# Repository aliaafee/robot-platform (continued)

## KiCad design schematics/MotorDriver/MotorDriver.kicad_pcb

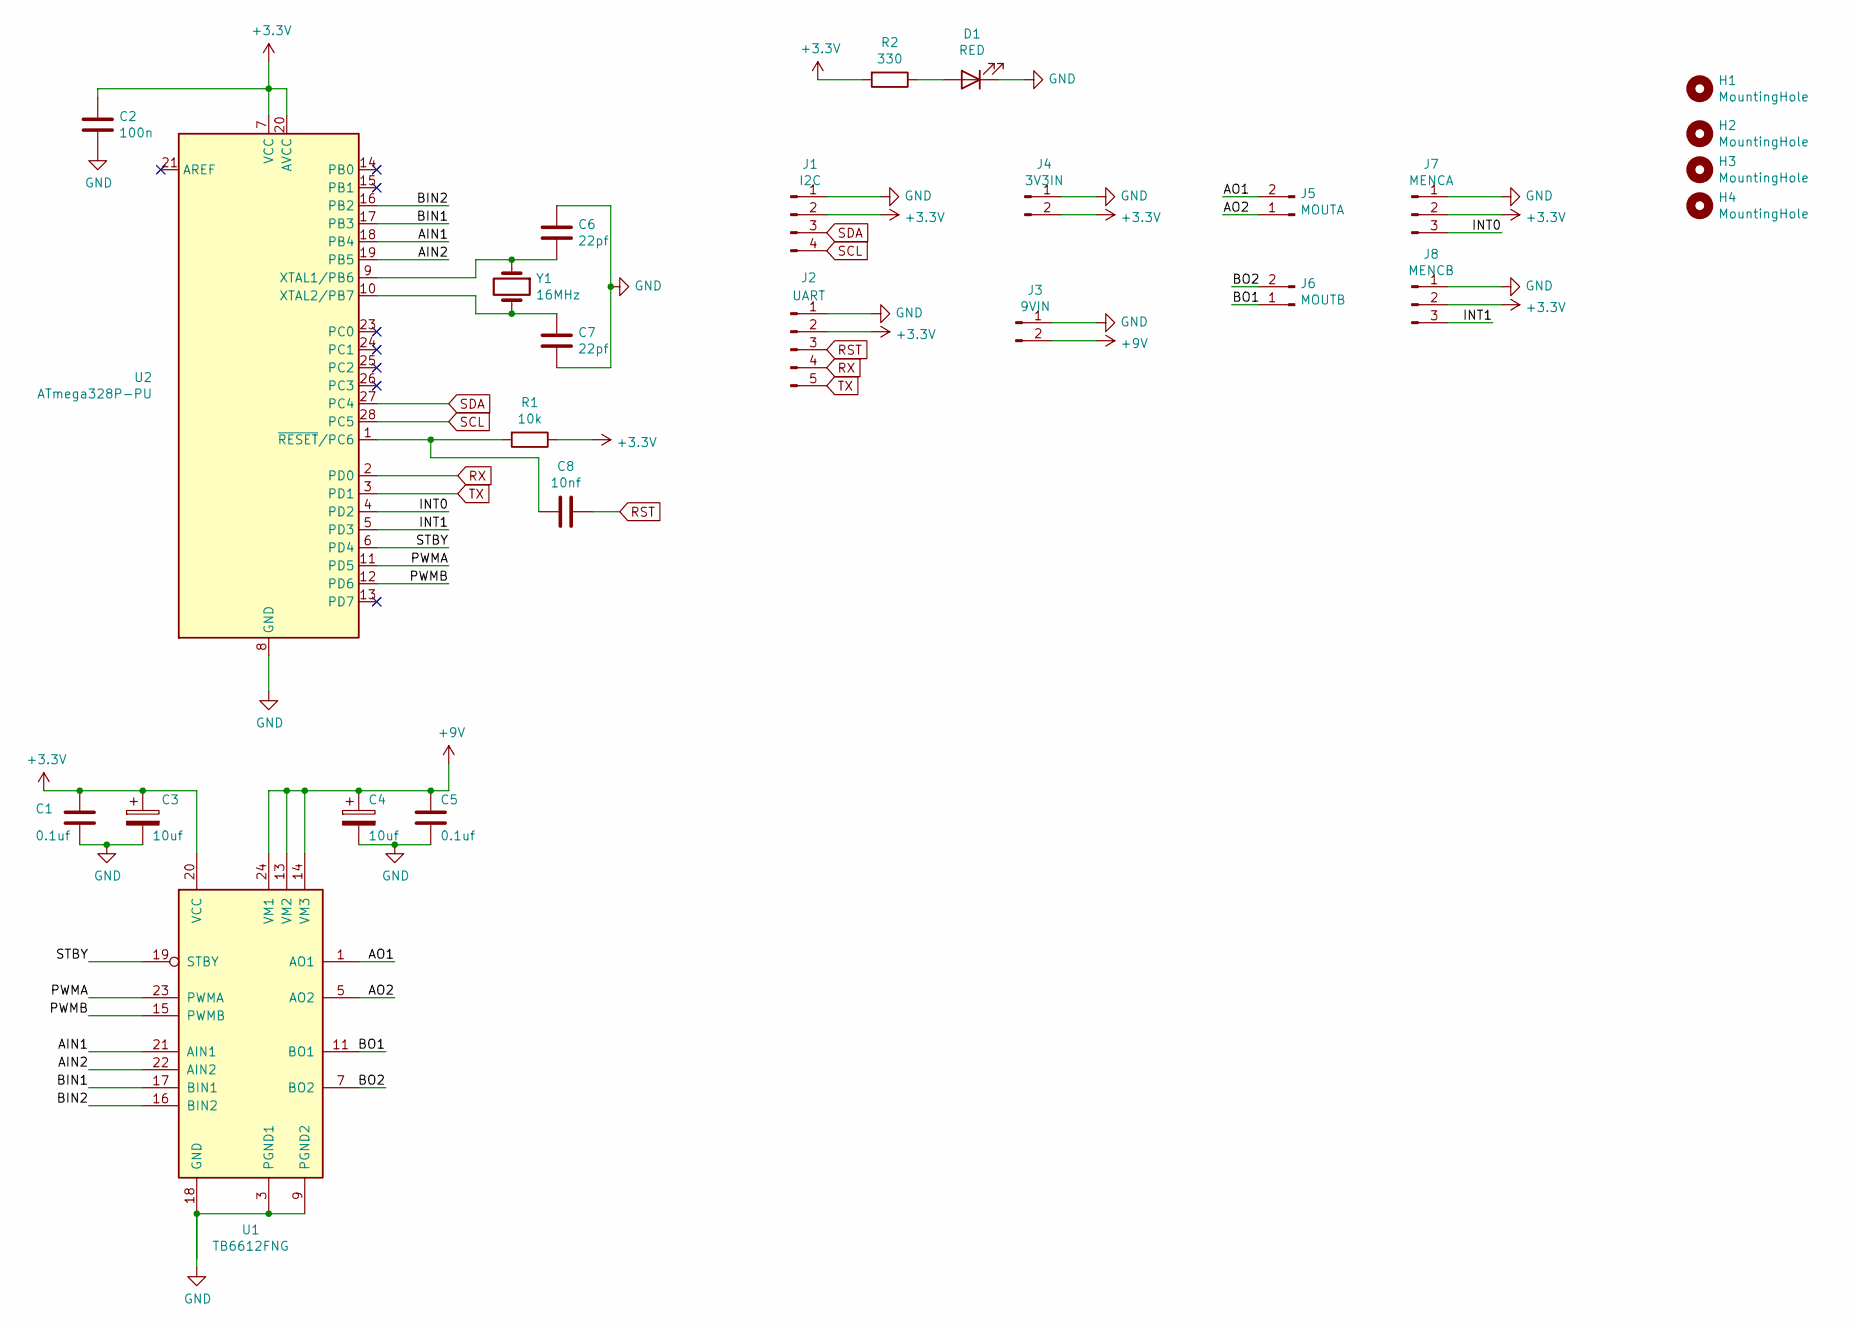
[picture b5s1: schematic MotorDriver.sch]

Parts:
C1, C5: 0.1uf; C_1206_3216Metric
C2: 100n; C_1206_3216Metric
C3, C4: 10uf; CP_Elec_3x5.3
C6, C7: 22pf; C_1206_3216Metric
C8: 10nf; C_1206_3216Metric
D1: RED; LED_1206_3216Metric
H1, H2, H3, H4: MountingHole; MountingHole_2.5mm_Pad_TopBottom
J1: I2C; JST_XH_B4B-XH-A_1x04_P2.50mm_Vertical
J2: UART; PinHeader_1x05_P2.54mm_Vertical
J3: 9VIN; JST_XH_B2B-XH-A_1x02_P2.50mm_Vertical
J4: 3V3IN; JST_XH_B2B-XH-A_1x02_P2.50mm_Vertical
J5: MOUTA; JST_XH_B2B-XH-A_1x02_P2.50mm_Vertical
J6: MOUTB; JST_XH_B2B-XH-A_1x02_P2.50mm_Vertical
J7: MENCA; JST_XH_B3B-XH-A_1x03_P2.50mm_Vertical
J8: MENCB; JST_XH_B3B-XH-A_1x03_P2.50mm_Vertical
R1: 10k; R_1206_3216Metric
R2: 330; R_1206_3216Metric
U1: TB6612FNG; SSOP-24_5.3x8.2mm_P0.65mm
U2: ATmega328P-PU; DIP-28_W7.62mm
Y1: 16MHz; Crystal_HC49-4H_Vertical

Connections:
+3V3: C1.1, C2.2, C3.1, J1.2, J2.2, J4.2, J7.2, J8.2, R1.1, R2.2, U1.20 (VCC), U2.7 (VCC), U2.20 (AVCC)
+9V: C4.1, C5.1, J3.2, U1.13 (VM2), U1.14 (VM3), U1.24 (VM1)
/AIN1: U1.21 (AIN1), U2.18 (PB4)
/AIN2: U1.22 (AIN2), U2.19 (PB5)
/AO1: J5.2, U1.1 (AO1), U1.2 (AO1)
/AO2: J5.1, U1.5 (AO2), U1.6 (AO2)
/BIN1: U1.17 (BIN1), U2.17 (PB3)
/BIN2: U1.16 (BIN2), U2.16 (PB2)
/BO1: J6.1, U1.11 (BO1), U1.12 (BO1)
/BO2: J6.2, U1.7 (BO2), U1.8 (BO2)
/INT0: J7.3, U2.4 (PD2)
/INT1: J8.3, U2.5 (PD3)
/PWMA: U1.23 (PWMA), U2.11 (PD5)
/PWMB: U1.15 (PWMB), U2.12 (PD6)
/STBY: U1.19 (STBY), U2.6 (PD4)
GND: C1.2, C2.1, C3.2, C4.2, C5.2, C6.2, C7.2, D1.1 (K), J1.1, J2.1, J3.1, J4.1, J7.1, J8.1, U1.3 (PGND1), U1.4 (PGND1), U1.9 (PGND2), U1.10 (PGND2), U1.18 (GND), U2.8 (GND), U2.22 (GND)
unnamed: C6.1, U2.9 (XTAL1/PB6), Y1.1
unnamed: C7.1, U2.10 (XTAL2/PB7), Y1.2
unnamed: C8.2, R1.2, U2.1 (~RESET~/PC6)
unnamed: D1.2 (A), R2.1
RST: C8.1, J2.3
RX: J2.4, U2.2 (PD0)
SCL: J1.4, U2.28 (PC5)
SDA: J1.3, U2.27 (PC4)
TX: J2.5, U2.3 (PD1)

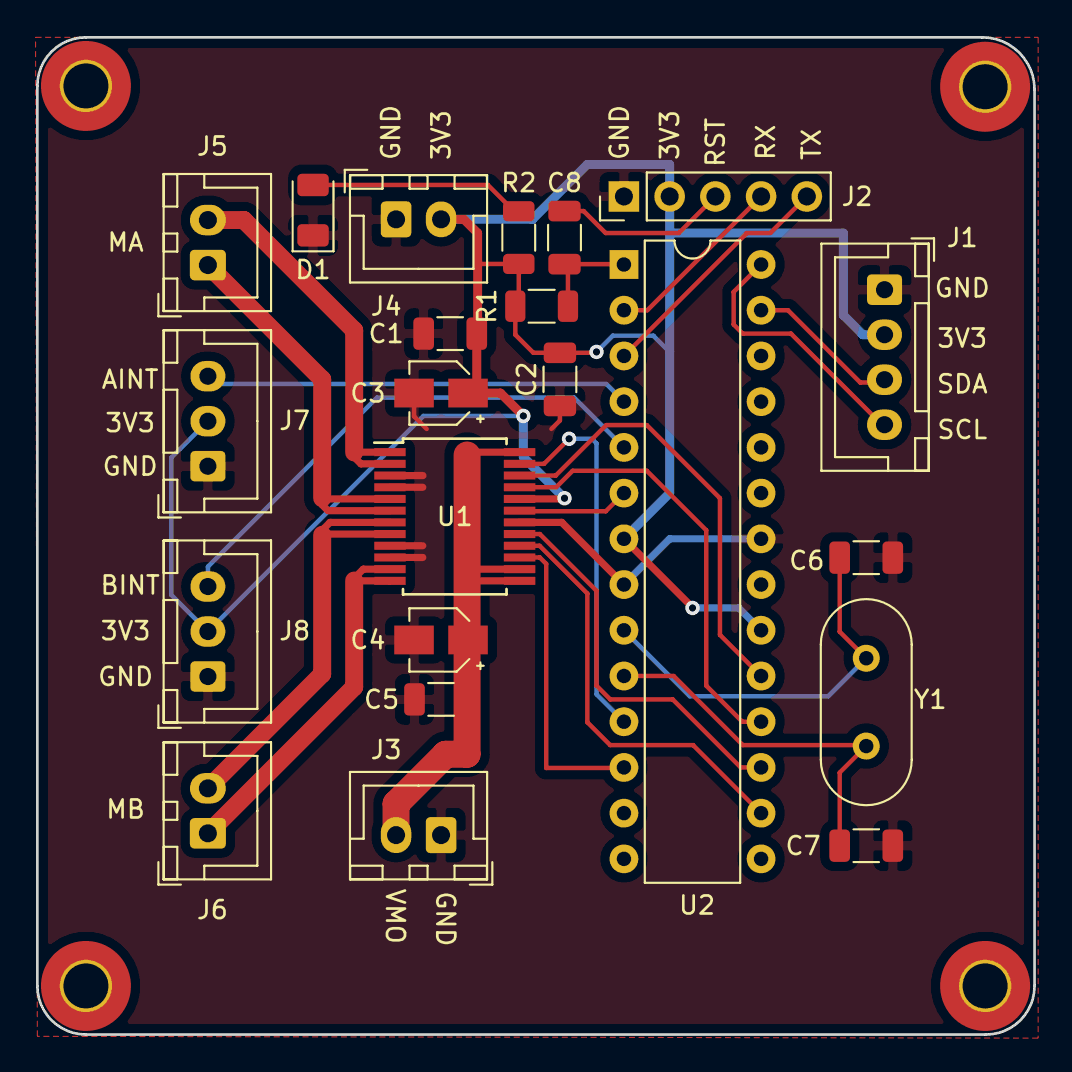
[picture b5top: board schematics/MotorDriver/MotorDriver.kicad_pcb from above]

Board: 2 copper layers, 55.4 x 55.4 mm, 26 parts (0 on the bottom side), 25 nets.

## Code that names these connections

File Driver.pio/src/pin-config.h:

#ifndef PIN_CONFIG_H
#define PIN_CONFIG_H

#include <Arduino.h>

#define PWMB 11
#define BIN2 10
#define BIN1 9

#define STBY 8

#define AIN1 6
#define AIN2 7
#define PWMA 5


#define AENC1 2
#define AENC2 12

#define BENC1 3
#define BENC2 13

#endif

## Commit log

2021-10-12 Looking for stuff
2021-10-12 Robot Driver converted to platformio
2021-10-15 Organize
2021-10-19 Working on motor controller
2021-10-19 refactor
2021-10-20 Updated BOM
2021-10-20 Added docs
2021-10-26 Motor driver
2021-10-26 Added Caps
2021-10-30 Added robot hat
2021-10-30 Completed Robot Had for RaspberryPi
2021-10-31 Re organizing
2021-11-02 Arduino runs at 5v with logic level shifter on i2c bus
2021-11-02 Hehe
2021-11-06 other
2021-11-07 This
2023-08-25 Motor encoder with pid control
2023-09-01 Forward and backward pid control and encoder
2023-11-03 Robot control python program works
2024-12-07 Made some changed to make control more resilient to bus drop outs, and also motor stats visible
2024-12-07 Ability to read registers now added
2024-12-11 Fixed choppy i2c connection and added some features
2024-12-11 Updates to maintain compatibility with motor controller
